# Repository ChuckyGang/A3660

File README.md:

# A3660 -  The first open Seminative 68060 solution for bigbox Amigas

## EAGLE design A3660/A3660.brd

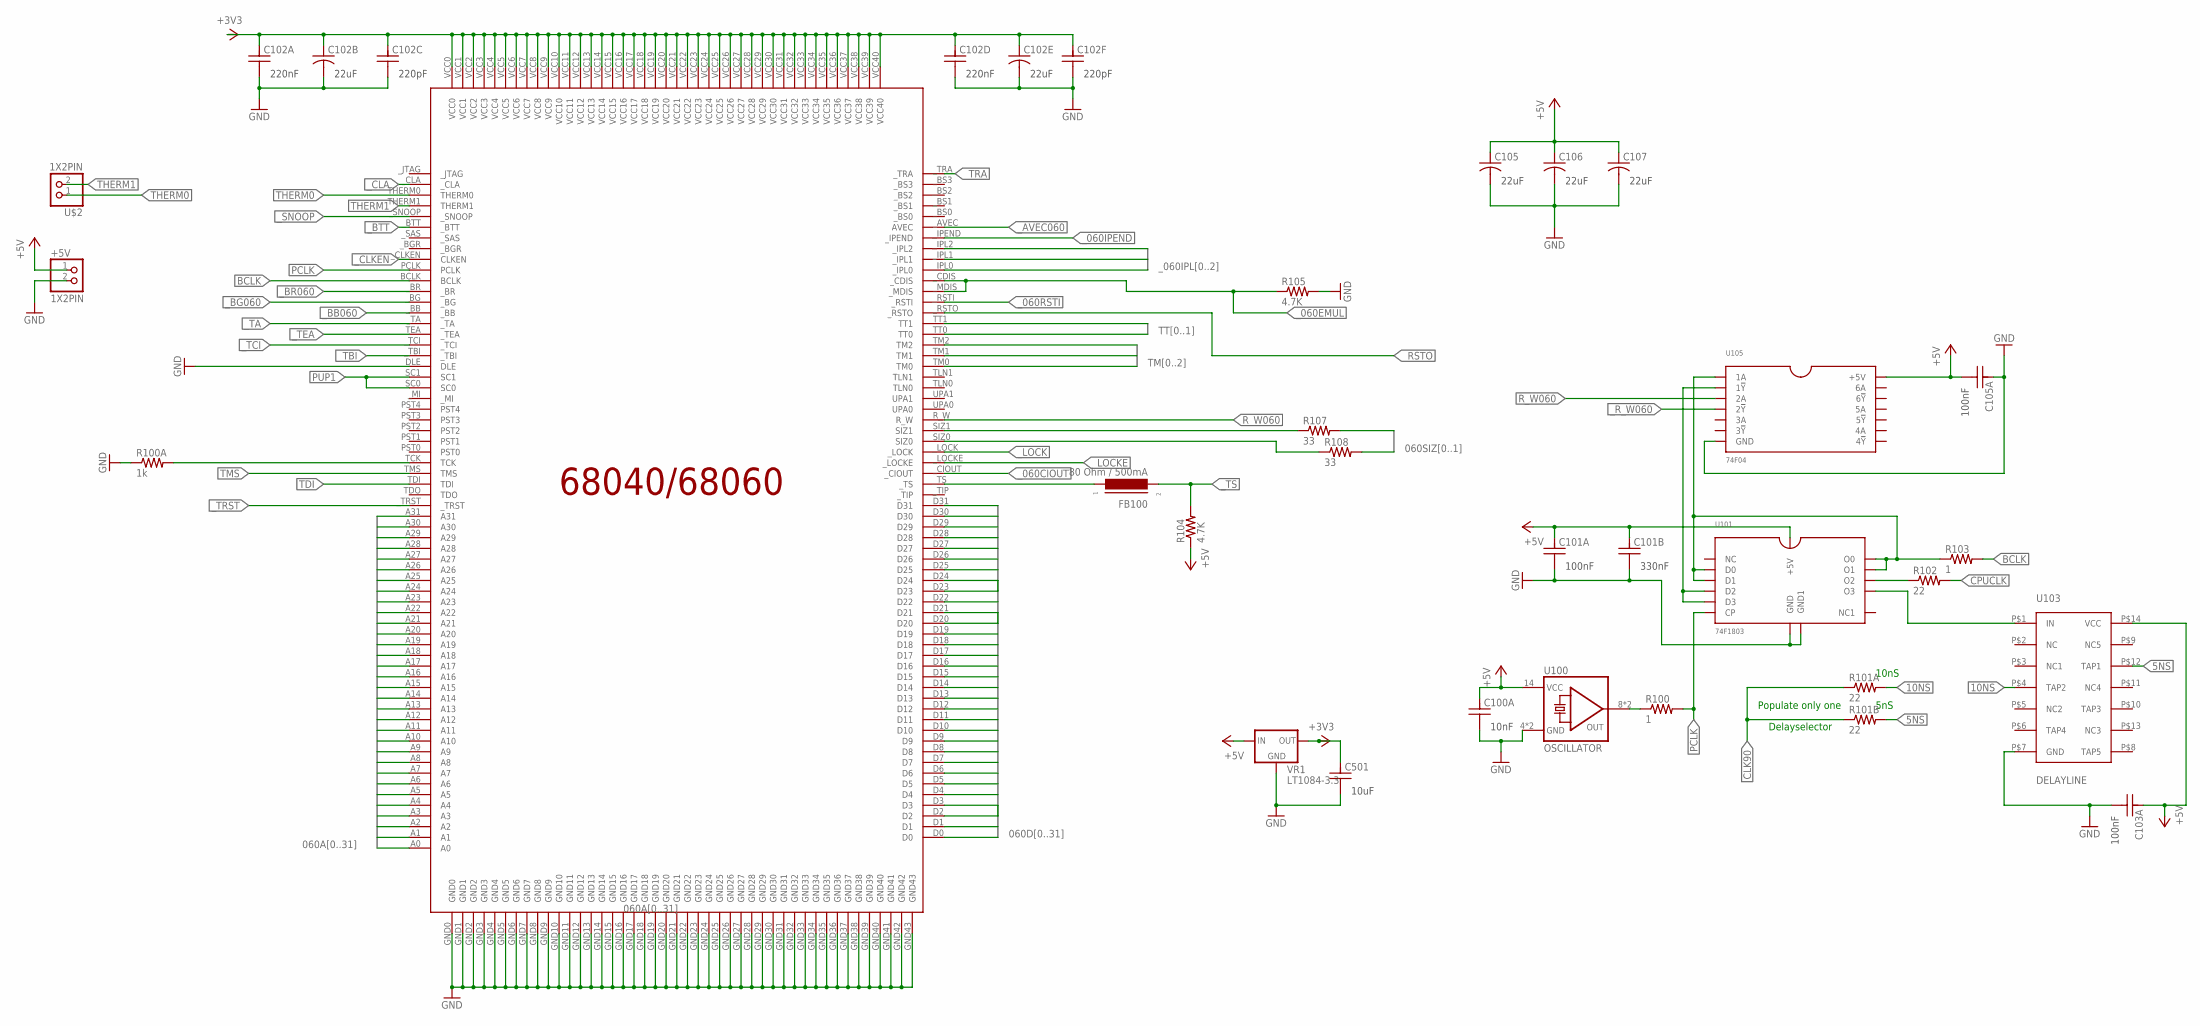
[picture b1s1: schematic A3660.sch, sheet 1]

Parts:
+5V: 1X2PIN
C100A: 10nF; R0805
C101A, C103A, C105A: 100nF; R0805
C101B: 330nF; R0805
C102A, C102D: 220nF; R0805
C102B, C102E, C105, C106, C107: 22uF; SMD-ELECTROLYTE
C102C, C102F: 220pF; R0805
C501: 10uF; R0805
FB100: 80 Ohm / 500mA; FERRITE
R100, R103: 1; R0805
R100A: 1k; R0805
R101A, R101B, R102: 22; R0805
R104, R105: 4.7K; R0805
R107, R108: 33; R0805
U100: OSCILLATOR
U101: 74F1803
U102: MC68040/68060
U103: DELAYLINE
U105: 74F04
U$2: 1X2PIN
VR1: LT1084-3.3

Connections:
5NS: R101B.2, U103.P$12 (TAP1)
10NS: R101A.2, U103.P$4 (TAP2)
060A0: U102.A0; also elsewhere on the board
060A1: U102.A1; also elsewhere on the board
060A2: U102.A2; also elsewhere on the board
060A3: U102.A3; also elsewhere on the board
060A4: U102.A4; also elsewhere on the board
060A5: U102.A5; also elsewhere on the board
060A6: U102.A6; also elsewhere on the board
060A7: U102.A7; also elsewhere on the board
060A8: U102.A8; also elsewhere on the board
060A9: U102.A9; also elsewhere on the board
060A10: U102.A10; also elsewhere on the board
060A11: U102.A11; also elsewhere on the board
060A12: U102.A12; also elsewhere on the board
060A13: U102.A13; also elsewhere on the board
060A14: U102.A14; also elsewhere on the board
060A15: U102.A15; also elsewhere on the board
060A16: U102.A16; also elsewhere on the board
060A17: U102.A17; also elsewhere on the board
060A18: U102.A18; also elsewhere on the board
060A19: U102.A19; also elsewhere on the board
060A20: U102.A20; also elsewhere on the board
060A21: U102.A21; also elsewhere on the board
060A22: U102.A22; also elsewhere on the board
060A23: U102.A23; also elsewhere on the board
060A24: U102.A24; also elsewhere on the board
060A25: U102.A25; also elsewhere on the board
060A26: U102.A26; also elsewhere on the board
060A27: U102.A27; also elsewhere on the board
060A28: U102.A28; also elsewhere on the board
060A29: U102.A29; also elsewhere on the board
060A30: U102.A30; also elsewhere on the board
060A31: U102.A31; also elsewhere on the board
060D0: U102.D0; also elsewhere on the board
060D1: U102.D1; also elsewhere on the board
060D2: U102.D2; also elsewhere on the board
060D3: U102.D3; also elsewhere on the board
060D4: U102.D4; also elsewhere on the board
060D5: U102.D5; also elsewhere on the board
060D6: U102.D6; also elsewhere on the board
060D7: U102.D7; also elsewhere on the board
060D8: U102.D8; also elsewhere on the board
060D9: U102.D9; also elsewhere on the board
060D10: U102.D10; also elsewhere on the board
060D11: U102.D11; also elsewhere on the board
060D12: U102.D12; also elsewhere on the board
060D13: U102.D13; also elsewhere on the board
060D14: U102.D14; also elsewhere on the board
060D15: U102.D15; also elsewhere on the board
060D16: U102.D16; also elsewhere on the board
060D17: U102.D17; also elsewhere on the board
060D18: U102.D18; also elsewhere on the board
060D19: U102.D19; also elsewhere on the board
060D20: U102.D20; also elsewhere on the board
060D21: U102.D21; also elsewhere on the board
060D22: U102.D22; also elsewhere on the board
060D23: U102.D23; also elsewhere on the board
060D24: U102.D24; also elsewhere on the board
060D25: U102.D25; also elsewhere on the board
060D26: U102.D26; also elsewhere on the board
060D27: U102.D27; also elsewhere on the board
060D28: U102.D28; also elsewhere on the board
060D29: U102.D29; also elsewhere on the board
060D30: U102.D30; also elsewhere on the board
060D31: U102.D31; also elsewhere on the board
060SIZ0: R108.2; also elsewhere on the board
060SIZ1: R107.2; also elsewhere on the board
+3V3: C102A.1, C102B.+ (1), C102C.1, C102D.1, C102E.+ (1), C102F.1, C501.1, U102.VCC0, U102.VCC1, U102.VCC2, U102.VCC3, U102.VCC4, U102.VCC5, U102.VCC6, U102.VCC7, U102.VCC8, U102.VCC9, U102.VCC10, U102.VCC11, U102.VCC12, U102.VCC13, U102.VCC14, U102.VCC15, U102.VCC16, U102.VCC17, U102.VCC18, U102.VCC19, U102.VCC20, U102.VCC21, U102.VCC22, U102.VCC23, U102.VCC24, U102.VCC25, U102.VCC26, U102.VCC27, U102.VCC28, U102.VCC29, U102.VCC30, U102.VCC31, U102.VCC32, U102.VCC33, U102.VCC34, U102.VCC35, U102.VCC36, U102.VCC37, U102.VCC38, U102.VCC39, U102.VCC40, VR1.OUT, VR1.OUT2 (OUT); also elsewhere on the board
+5V: +5V.1, C100A.1, C101A.1, C101B.1, C103A.1, C105.+ (1), C105A.2, C106.+ (1), C107.+ (1), R104.1, U100.14 (+5V), U101.14 (+5V), U103.P$14 (VCC), U105.14 (+5V), VR1.IN; also elsewhere on the board
BCLK: R103.2, U102.BCLK; also elsewhere on the board
CLK90: R101A.1, R101B.1; also elsewhere on the board
CPUCLK: R102.2; also elsewhere on the board
GND: +5V.2, C100A.2, C101A.2, C101B.2, C102A.2, C102B.- (2), C102C.2, C102D.2, C102E.- (2), C102F.2, C103A.2, C105.- (2), C105A.1, C106.- (2), C107.- (2), C501.2, R100A.1, R105.2, U100.4 (GND), U100.7 (GND), U101.1 (GND), U101.7 (GND1), U102.DLE, U102.GND0, U102.GND1, U102.GND2, U102.GND3, U102.GND4, U102.GND5, U102.GND6, U102.GND7, U102.GND8, U102.GND9, U102.GND10, U102.GND11, U102.GND12, U102.GND13, U102.GND14, U102.GND15, U102.GND16, U102.GND17, U102.GND18, U102.GND19, U102.GND20, U102.GND21, U102.GND22, U102.GND23, U102.GND24, U102.GND25, U102.GND26, U102.GND27, U102.GND28, U102.GND29, U102.GND30, U102.GND31, U102.GND32, U102.GND33, U102.GND34, U102.GND35, U102.GND36, U102.GND37, U102.GND38, U102.GND39, U102.GND40, U102.GND41, U102.GND42, U102.GND43, U103.P$7 (GND), U105.7 (GND), VR1.GND; also elsewhere on the board
unnamed: R107.1, U102.SIZ1
unnamed: R108.1, U102.SIZ0
unnamed: FB100.1, U102._TS
unnamed: R100.1, U100.8 (OUT), U100.11 (OUT)
unnamed: U101.10 (D2), U101.11 (D3), U105.2 (1!Y)
unnamed: R103.1, U101.3 (O0), U101.4 (D0), U101.5 (D1), U101.6 (O1), U105.1 (1A)
unnamed: R102.1, U101.9 (O2)
unnamed: U101.12 (O3), U103.P$1 (IN)
PCLK: R100.2, U101.8 (CP), U102.PCLK
PUP1: U102.SC0, U102.SC1; also elsewhere on the board
R_W060: U102.R_W, U105.3 (2A); also elsewhere on the board
TCK: R100A.2, U102.TCK
TDI: U102.TDI; also elsewhere on the board
THERM0: U102.THERM0, U$2.1
THERM1: U102.THERM1, U$2.2
TM0: U102.TM0; also elsewhere on the board
TM1: U102.TM1; also elsewhere on the board
TM2: U102.TM2; also elsewhere on the board
TMS: U102.TMS; also elsewhere on the board
TT0: U102.TT0; also elsewhere on the board
TT1: U102.TT1; also elsewhere on the board
_060CIOUT: U102._CIOUT; also elsewhere on the board
_060EMUL: R105.1, U102._CDIS, U102._MDIS; also elsewhere on the board
_060IPEND: U102._IPEND; also elsewhere on the board
_060IPL0: U102._IPL0; also elsewhere on the board
_060IPL1: U102._IPL1; also elsewhere on the board
_060IPL2: U102._IPL2; also elsewhere on the board
_060RSTI: U102._RSTI; also elsewhere on the board
_AVEC060: U102._AVEC (AVEC); also elsewhere on the board
_BB060: U102._BB; also elsewhere on the board
_BG060: U102._BG; also elsewhere on the board
_BR060: U102._BR; also elsewhere on the board
_BTT: U102._BTT; also elsewhere on the board
_CLA: U102._CLA; also elsewhere on the board
_CLKEN: U102._CLKEN (CLKEN); also elsewhere on the board
_LOCK: U102._LOCK; also elsewhere on the board
_LOCKE: U102._LOCKE; also elsewhere on the board
_RSTO: U102._RSTO; also elsewhere on the board
_R_W060: U105.4 (2!Y); also elsewhere on the board
_SNOOP: U102._SNOOP; also elsewhere on the board
_TA: U102._TA; also elsewhere on the board
_TBI: U102._TBI; also elsewhere on the board
_TCI: U102._TCI; also elsewhere on the board
_TEA: U102._TEA; also elsewhere on the board
_TRA: U102._TRA; also elsewhere on the board
_TRST: U102._TRST; also elsewhere on the board
_TS: FB100.2, R104.2; also elsewhere on the board

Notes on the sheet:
10nS
5nS
Populate only one
Delayselector

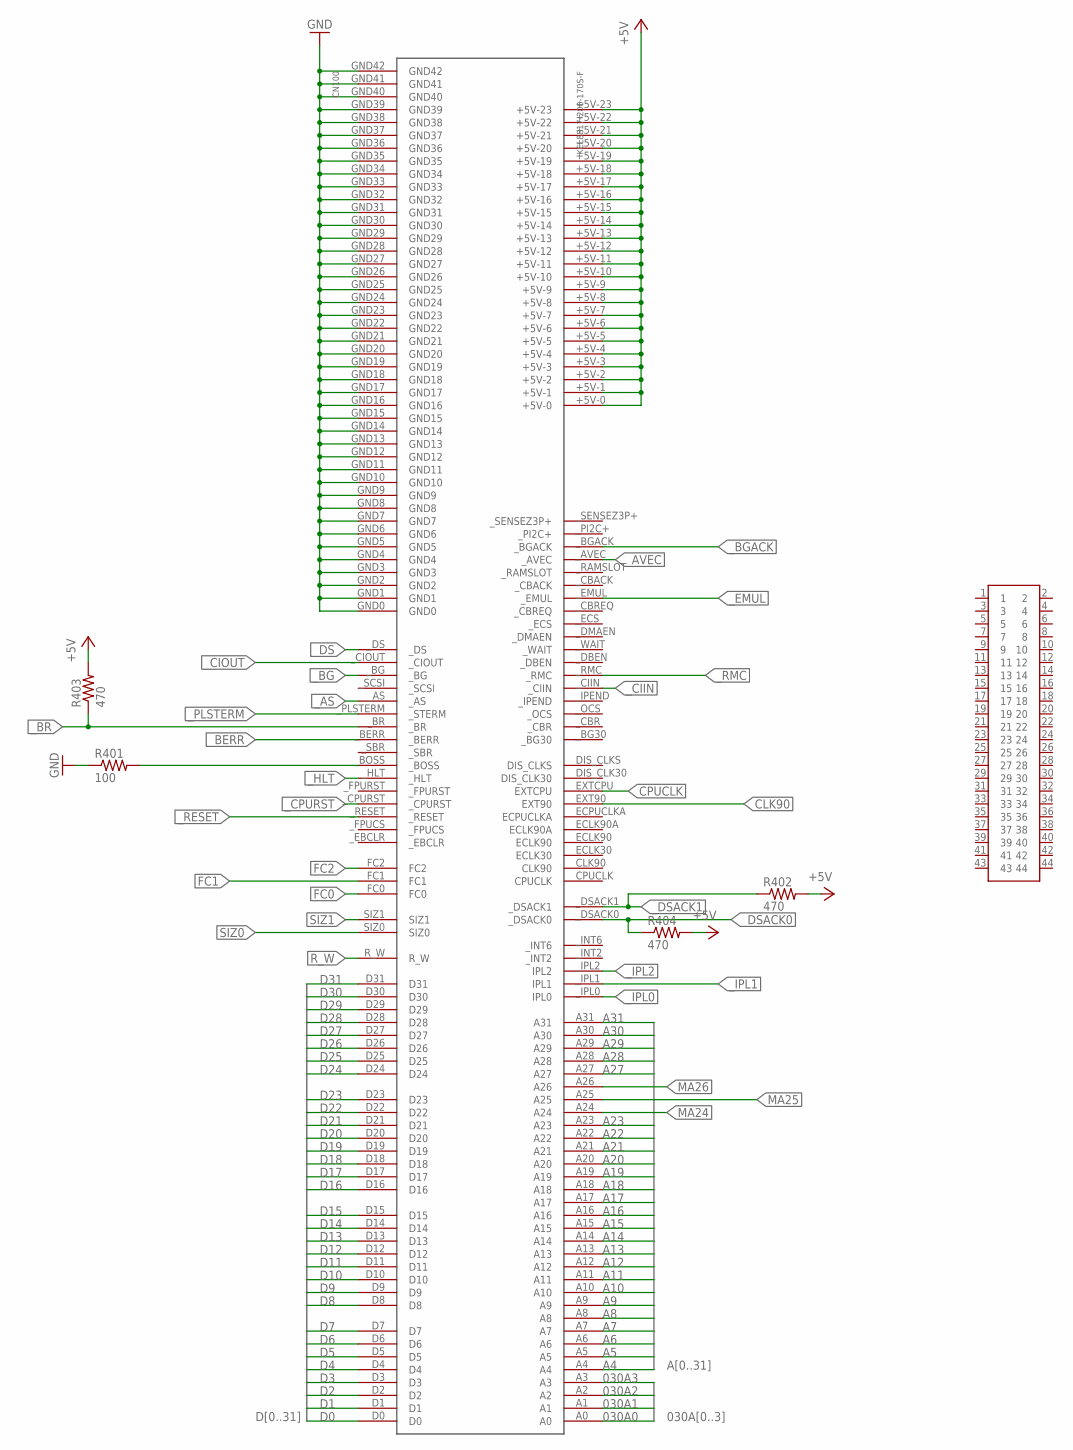
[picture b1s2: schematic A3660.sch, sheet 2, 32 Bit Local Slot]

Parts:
CN100: KEL8817-200-170S-F
R401: 100; R0805
R402, R403, R404: 470; R0805
U$1: 2X22-2MM; 2X22

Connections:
030A0: CN100.A0; also elsewhere on the board
030A1: CN100.A1; also elsewhere on the board
030A2: CN100.A2; also elsewhere on the board
030A3: CN100.A3; also elsewhere on the board
+5V: CN100.+5V-0, CN100.+5V-1, CN100.+5V-2, CN100.+5V-3, CN100.+5V-4, CN100.+5V-5, CN100.+5V-6, CN100.+5V-7, CN100.+5V-8, CN100.+5V-9, CN100.+5V-10, CN100.+5V-11, CN100.+5V-12, CN100.+5V-13, CN100.+5V-14, CN100.+5V-15, CN100.+5V-16, CN100.+5V-17, CN100.+5V-18, CN100.+5V-19, CN100.+5V-20, CN100.+5V-21, CN100.+5V-22, CN100.+5V-23, R402.2, R403.2, R404.2; also elsewhere on the board
A4: CN100.A4; also elsewhere on the board
A5: CN100.A5; also elsewhere on the board
A6: CN100.A6; also elsewhere on the board
A7: CN100.A7; also elsewhere on the board
A8: CN100.A8; also elsewhere on the board
A9: CN100.A9; also elsewhere on the board
A10: CN100.A10; also elsewhere on the board
A11: CN100.A11; also elsewhere on the board
A12: CN100.A12; also elsewhere on the board
A13: CN100.A13; also elsewhere on the board
A14: CN100.A14; also elsewhere on the board
A15: CN100.A15; also elsewhere on the board
A16: CN100.A16; also elsewhere on the board
A17: CN100.A17; also elsewhere on the board
A18: CN100.A18; also elsewhere on the board
A19: CN100.A19; also elsewhere on the board
A20: CN100.A20; also elsewhere on the board
A21: CN100.A21; also elsewhere on the board
A22: CN100.A22; also elsewhere on the board
A23: CN100.A23; also elsewhere on the board
A27: CN100.A27; also elsewhere on the board
A28: CN100.A28; also elsewhere on the board
A29: CN100.A29; also elsewhere on the board
A30: CN100.A30; also elsewhere on the board
A31: CN100.A31; also elsewhere on the board
CLK90: CN100.EXT90; also elsewhere on the board
CPUCLK: CN100.EXTCPU; also elsewhere on the board
D0: CN100.D0; also elsewhere on the board
D1: CN100.D1; also elsewhere on the board
D2: CN100.D2; also elsewhere on the board
D3: CN100.D3; also elsewhere on the board
D4: CN100.D4; also elsewhere on the board
D5: CN100.D5; also elsewhere on the board
D6: CN100.D6; also elsewhere on the board
D7: CN100.D7; also elsewhere on the board
D8: CN100.D8; also elsewhere on the board
D9: CN100.D9; also elsewhere on the board
D10: CN100.D10; also elsewhere on the board
D11: CN100.D11; also elsewhere on the board
D12: CN100.D12; also elsewhere on the board
D13: CN100.D13; also elsewhere on the board
D14: CN100.D14; also elsewhere on the board
D15: CN100.D15; also elsewhere on the board
D16: CN100.D16; also elsewhere on the board
D17: CN100.D17; also elsewhere on the board
D18: CN100.D18; also elsewhere on the board
D19: CN100.D19; also elsewhere on the board
D20: CN100.D20; also elsewhere on the board
D21: CN100.D21; also elsewhere on the board
D22: CN100.D22; also elsewhere on the board
D23: CN100.D23; also elsewhere on the board
D24: CN100.D24; also elsewhere on the board
D25: CN100.D25; also elsewhere on the board
D26: CN100.D26; also elsewhere on the board
D27: CN100.D27; also elsewhere on the board
D28: CN100.D28; also elsewhere on the board
D29: CN100.D29; also elsewhere on the board
D30: CN100.D30; also elsewhere on the board
D31: CN100.D31; also elsewhere on the board
FC0: CN100.FC0; also elsewhere on the board
FC1: CN100.FC1; also elsewhere on the board
FC2: CN100.FC2; also elsewhere on the board
GND: CN100.GND0, CN100.GND1, CN100.GND2, CN100.GND3, CN100.GND4, CN100.GND5, CN100.GND6, CN100.GND7, CN100.GND8, CN100.GND9, CN100.GND10, CN100.GND11, CN100.GND12, CN100.GND13, CN100.GND14, CN100.GND15, CN100.GND16, CN100.GND17, CN100.GND18, CN100.GND19, CN100.GND20, CN100.GND21, CN100.GND22, CN100.GND23, CN100.GND24, CN100.GND25, CN100.GND26, CN100.GND27, CN100.GND28, CN100.GND29, CN100.GND30, CN100.GND31, CN100.GND32, CN100.GND33, CN100.GND34, CN100.GND35, CN100.GND36, CN100.GND37, CN100.GND38, CN100.GND39, CN100.GND40, CN100.GND41, CN100.GND42, R401.1; also elsewhere on the board
MA24: CN100.A24; also elsewhere on the board
MA25: CN100.A25; also elsewhere on the board
MA26: CN100.A26; also elsewhere on the board
unnamed: CN100._BOSS, R401.2
R_W: CN100.R_W; also elsewhere on the board
SIZ0: CN100.SIZ0; also elsewhere on the board
SIZ1: CN100.SIZ1; also elsewhere on the board
_AS: CN100._AS; also elsewhere on the board
_AVEC: CN100._AVEC; also elsewhere on the board
_BERR: CN100._BERR; also elsewhere on the board
_BG: CN100._BG; also elsewhere on the board
_BGACK: CN100._BGACK; also elsewhere on the board
_BR: CN100._BR, R403.1; also elsewhere on the board
_CIIN: CN100._CIIN; also elsewhere on the board
_CIOUT: CN100._CIOUT; also elsewhere on the board
_CPURST: CN100._CPURST; also elsewhere on the board
_DS: CN100._DS; also elsewhere on the board
_DSACK0: CN100._DSACK0, R404.1; also elsewhere on the board
_DSACK1: CN100._DSACK1, R402.1; also elsewhere on the board
_EMUL: CN100._EMUL; also elsewhere on the board
_HLT: CN100._HLT; also elsewhere on the board
_IPL0: CN100._IPL0 (IPL0); also elsewhere on the board
_IPL1: CN100._IPL1 (IPL1); also elsewhere on the board
_IPL2: CN100._IPL2 (IPL2); also elsewhere on the board
_PLSTERM: CN100._PLSTERM (_STERM); also elsewhere on the board
_RESET: CN100._RESET; also elsewhere on the board
_RMC: CN100._RMC; also elsewhere on the board

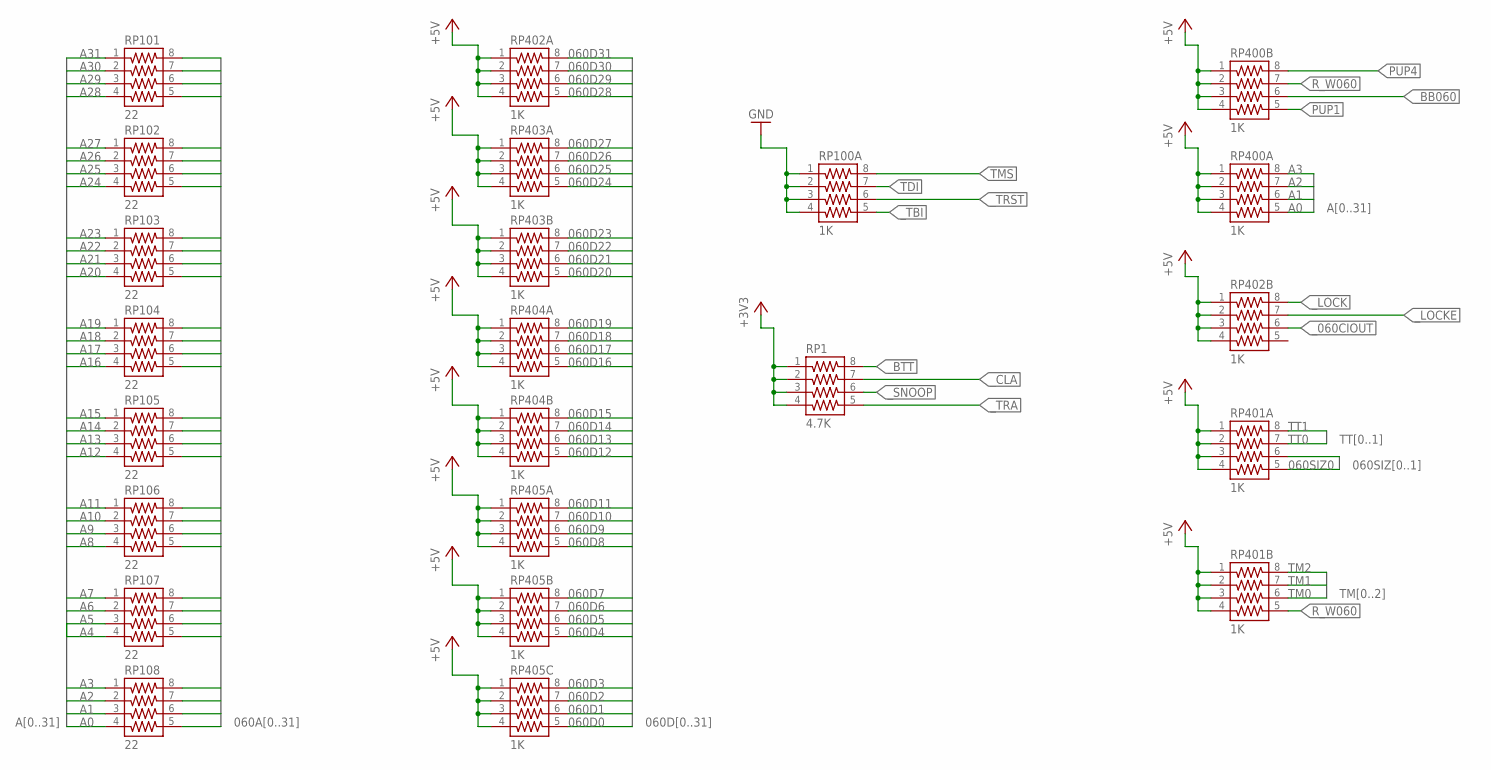
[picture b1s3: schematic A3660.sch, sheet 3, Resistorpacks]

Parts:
RP1: 4.7K; RP743-8
RP100A, RP400A, RP400B, RP401A, RP401B, RP402A, RP402B, RP403A, RP403B, RP404A, RP404B, RP405A, RP405B, RP405C: 1K; RP743-8
RP101, RP102, RP103, RP104, RP105, RP106, RP107, RP108: 22; RP743-8

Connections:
060A0: RP108.5; also elsewhere on the board
060A1: RP108.6; also elsewhere on the board
060A2: RP108.7; also elsewhere on the board
060A3: RP108.8; also elsewhere on the board
060A4: RP107.5; also elsewhere on the board
060A5: RP107.6; also elsewhere on the board
060A6: RP107.7; also elsewhere on the board
060A7: RP107.8; also elsewhere on the board
060A8: RP106.5; also elsewhere on the board
060A9: RP106.6; also elsewhere on the board
060A10: RP106.7; also elsewhere on the board
060A11: RP106.8; also elsewhere on the board
060A12: RP105.5; also elsewhere on the board
060A13: RP105.6; also elsewhere on the board
060A14: RP105.7; also elsewhere on the board
060A15: RP105.8; also elsewhere on the board
060A16: RP104.5; also elsewhere on the board
060A17: RP104.6; also elsewhere on the board
060A18: RP104.7; also elsewhere on the board
060A19: RP104.8; also elsewhere on the board
060A20: RP103.5; also elsewhere on the board
060A21: RP103.6; also elsewhere on the board
060A22: RP103.7; also elsewhere on the board
060A23: RP103.8; also elsewhere on the board
060A24: RP102.5; also elsewhere on the board
060A25: RP102.6; also elsewhere on the board
060A26: RP102.7; also elsewhere on the board
060A27: RP102.8; also elsewhere on the board
060A28: RP101.5; also elsewhere on the board
060A29: RP101.6; also elsewhere on the board
060A30: RP101.7; also elsewhere on the board
060A31: RP101.8; also elsewhere on the board
060D0: RP405C.5; also elsewhere on the board
060D1: RP405C.6; also elsewhere on the board
060D2: RP405C.7; also elsewhere on the board
060D3: RP405C.8; also elsewhere on the board
060D4: RP405B.5; also elsewhere on the board
060D5: RP405B.6; also elsewhere on the board
060D6: RP405B.7; also elsewhere on the board
060D7: RP405B.8; also elsewhere on the board
060D8: RP405A.5; also elsewhere on the board
060D9: RP405A.6; also elsewhere on the board
060D10: RP405A.7; also elsewhere on the board
060D11: RP405A.8; also elsewhere on the board
060D12: RP404B.5; also elsewhere on the board
060D13: RP404B.6; also elsewhere on the board
060D14: RP404B.7; also elsewhere on the board
060D15: RP404B.8; also elsewhere on the board
060D16: RP404A.5; also elsewhere on the board
060D17: RP404A.6; also elsewhere on the board
060D18: RP404A.7; also elsewhere on the board
060D19: RP404A.8; also elsewhere on the board
060D20: RP403B.5; also elsewhere on the board
060D21: RP403B.6; also elsewhere on the board
060D22: RP403B.7; also elsewhere on the board
060D23: RP403B.8; also elsewhere on the board
060D24: RP403A.5; also elsewhere on the board
060D25: RP403A.6; also elsewhere on the board
060D26: RP403A.7; also elsewhere on the board
060D27: RP403A.8; also elsewhere on the board
060D28: RP402A.5; also elsewhere on the board
060D29: RP402A.6; also elsewhere on the board
060D30: RP402A.7; also elsewhere on the board
060D31: RP402A.8; also elsewhere on the board
060SIZ0: RP401A.5; also elsewhere on the board
060SIZ1: RP401A.6; also elsewhere on the board
+3V3: RP1.1, RP1.2, RP1.3, RP1.4; also elsewhere on the board
+5V: RP400A.1, RP400A.2, RP400A.3, RP400A.4, RP400B.1, RP400B.2, RP400B.3, RP400B.4, RP401A.1, RP401A.2, RP401A.3, RP401A.4, RP401B.1, RP401B.2, RP401B.3, RP401B.4, RP402A.1, RP402A.2, RP402A.3, RP402A.4, RP402B.1, RP402B.2, RP402B.3, RP402B.4, RP403A.1, RP403A.2, RP403A.3, RP403A.4, RP403B.1, RP403B.2, RP403B.3, RP403B.4, RP404A.1, RP404A.2, RP404A.3, RP404A.4, RP404B.1, RP404B.2, RP404B.3, RP404B.4, RP405A.1, RP405A.2, RP405A.3, RP405A.4, RP405B.1, RP405B.2, RP405B.3, RP405B.4, RP405C.1, RP405C.2, RP405C.3, RP405C.4; also elsewhere on the board
A0: RP108.4, RP400A.5; also elsewhere on the board
A1: RP108.3, RP400A.6; also elsewhere on the board
A2: RP108.2, RP400A.7; also elsewhere on the board
A3: RP108.1, RP400A.8; also elsewhere on the board
A4: RP107.4; also elsewhere on the board
A5: RP107.3; also elsewhere on the board
A6: RP107.2; also elsewhere on the board
A7: RP107.1; also elsewhere on the board
A8: RP106.4; also elsewhere on the board
A9: RP106.3; also elsewhere on the board
A10: RP106.2; also elsewhere on the board
A11: RP106.1; also elsewhere on the board
A12: RP105.4; also elsewhere on the board
A13: RP105.3; also elsewhere on the board
A14: RP105.2; also elsewhere on the board
A15: RP105.1; also elsewhere on the board
A16: RP104.4; also elsewhere on the board
A17: RP104.3; also elsewhere on the board
A18: RP104.2; also elsewhere on the board
A19: RP104.1; also elsewhere on the board
A20: RP103.4; also elsewhere on the board
A21: RP103.3; also elsewhere on the board
A22: RP103.2; also elsewhere on the board
A23: RP103.1; also elsewhere on the board
A24: RP102.4; also elsewhere on the board
A25: RP102.3; also elsewhere on the board
A26: RP102.2; also elsewhere on the board
A27: RP102.1; also elsewhere on the board
A28: RP101.4; also elsewhere on the board
A29: RP101.3; also elsewhere on the board
A30: RP101.2; also elsewhere on the board
A31: RP101.1; also elsewhere on the board
GND: RP100A.1, RP100A.2, RP100A.3, RP100A.4; also elsewhere on the board
PUP1: RP400B.5; also elsewhere on the board
PUP4: RP400B.8; also elsewhere on the board
R_W060: RP400B.7, RP401B.5; also elsewhere on the board
TDI: RP100A.7; also elsewhere on the board
TM0: RP401B.6; also elsewhere on the board
TM1: RP401B.7; also elsewhere on the board
TM2: RP401B.8; also elsewhere on the board
TMS: RP100A.8; also elsewhere on the board
TT0: RP401A.7; also elsewhere on the board
TT1: RP401A.8; also elsewhere on the board
_060CIOUT: RP402B.6; also elsewhere on the board
_BB060: RP400B.6; also elsewhere on the board
_BTT: RP1.8; also elsewhere on the board
_CLA: RP1.7; also elsewhere on the board
_LOCK: RP402B.8; also elsewhere on the board
_LOCKE: RP402B.7; also elsewhere on the board
_SNOOP: RP1.6; also elsewhere on the board
_TBI: RP100A.5; also elsewhere on the board
_TRA: RP1.5; also elsewhere on the board
_TRST: RP100A.6; also elsewhere on the board
